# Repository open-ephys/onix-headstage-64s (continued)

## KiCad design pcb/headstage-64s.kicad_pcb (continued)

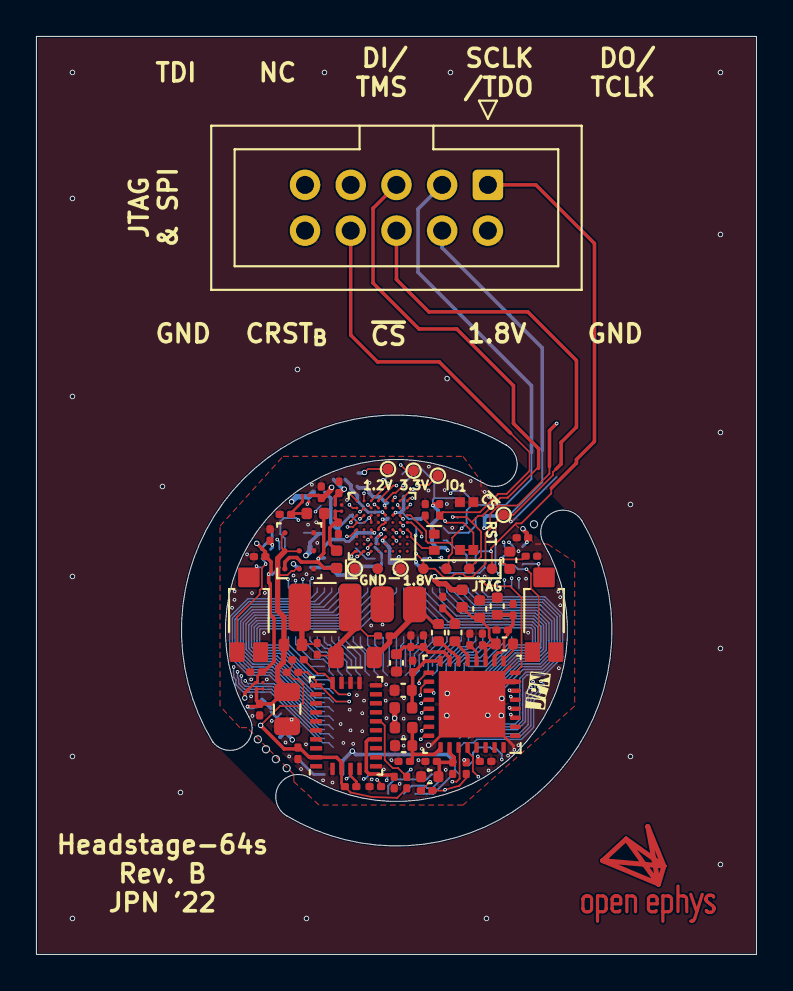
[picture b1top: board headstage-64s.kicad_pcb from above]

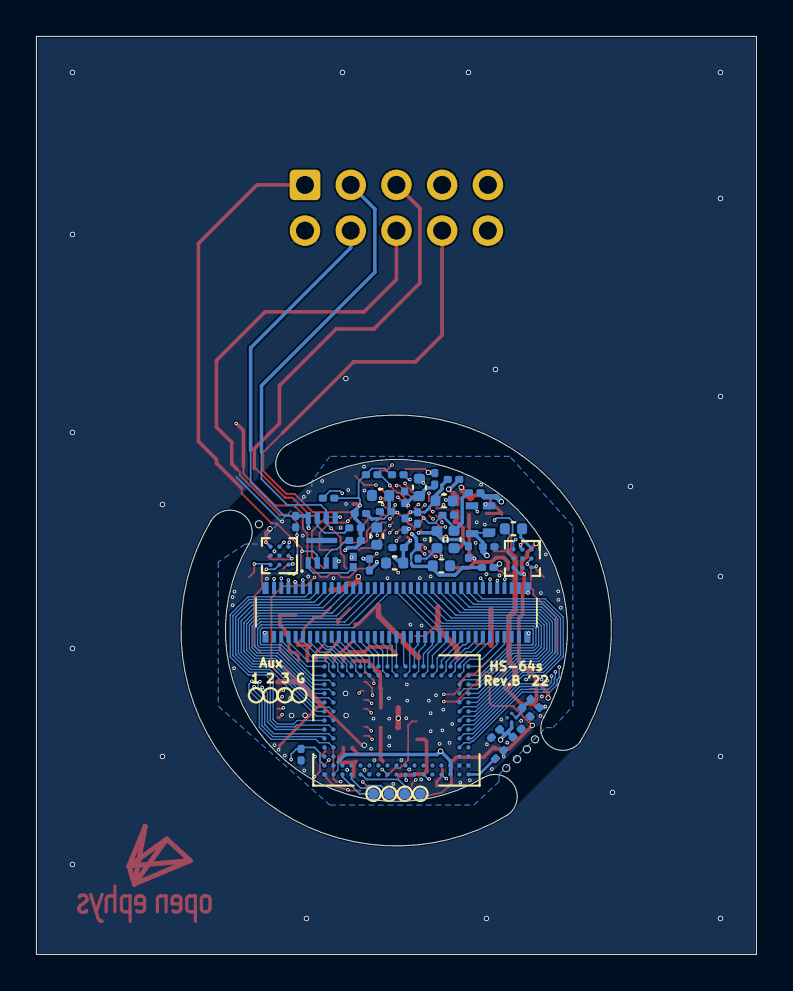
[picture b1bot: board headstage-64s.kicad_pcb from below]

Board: 6 copper layers, 40.0 x 51.0 mm, 120 parts (48 on the bottom side), 147 nets.

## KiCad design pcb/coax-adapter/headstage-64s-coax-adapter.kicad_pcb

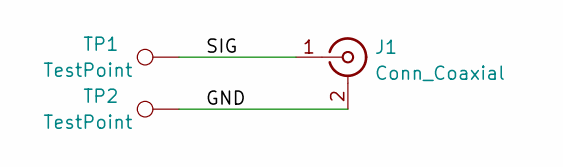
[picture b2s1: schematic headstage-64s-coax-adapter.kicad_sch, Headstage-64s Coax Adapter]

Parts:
J1: Conn_Coaxial; LINX_CONMHF4-SMD-G
TP1, TP2: TestPoint; Castellation

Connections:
/GND: J1.2 (Ext), TP2.1
/SIG: J1.1 (In), TP1.1

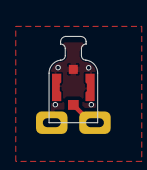
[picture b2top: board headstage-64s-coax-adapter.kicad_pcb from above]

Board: 2 copper layers, 2.7 x 4.8 mm, 4 parts (1 on the bottom side), 2 nets.

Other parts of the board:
kibuzzard-61EACC9F: G***; kibuzzard-61EACC9F

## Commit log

2022-01-18 Initial PCB design
    - This is a simplfied version of
    https://github.com/open-ephys/onix-headstage-64
    - Has the same features except for optical and electrical stimulation
    - Will need iterations when finalizing BOM and manufacturing details.
    - Targetting speedy 6-layer 0.6mm thick board. Epoxy filled and plated
    vias would be optimal, but I think I can get away without doing that.
2022-01-23 Added coax-adapter sub-board
    - 2-layer coaxial adapter sub-board for getting RA mount tether
    connection with integrated strain relief
    - The.step file is used for the 3D model in the local
    pcb/footprint/Coax-Adapter.kicad_mod
    - Local pcb/footprint/Castellation.kicad_mod is used for the castellated
    connectors on the coax-adapter itself
2022-01-23 Delete extra drill file
    - Mistakenly added in last commit
2022-01-25 Rev. A initial design prior to fab comments
    - BOM simplification
    - Added my initials to the board
    - Made the board more easy to panlize
2022-01-25 Added headstage-64s BOM
2022-03-02 Small changes before speedy fabrication
    - This is revision A
2022-12-06 Start of revision B
    - Address the following issues
    1. The photodiode anode is on pin 3, not pin 2
    2. No paste on coax connector
    3. CRESET_B needs to come out to programming header
    4. Need PU on CS line.
2022-12-06 Add a couple of missing files
2022-12-09 Remove coax-adapter pcb
    - It has been moved to its own repo since its used by several projects
2023-01-05 PCB revision B
    - Added production files sent from Speedy
